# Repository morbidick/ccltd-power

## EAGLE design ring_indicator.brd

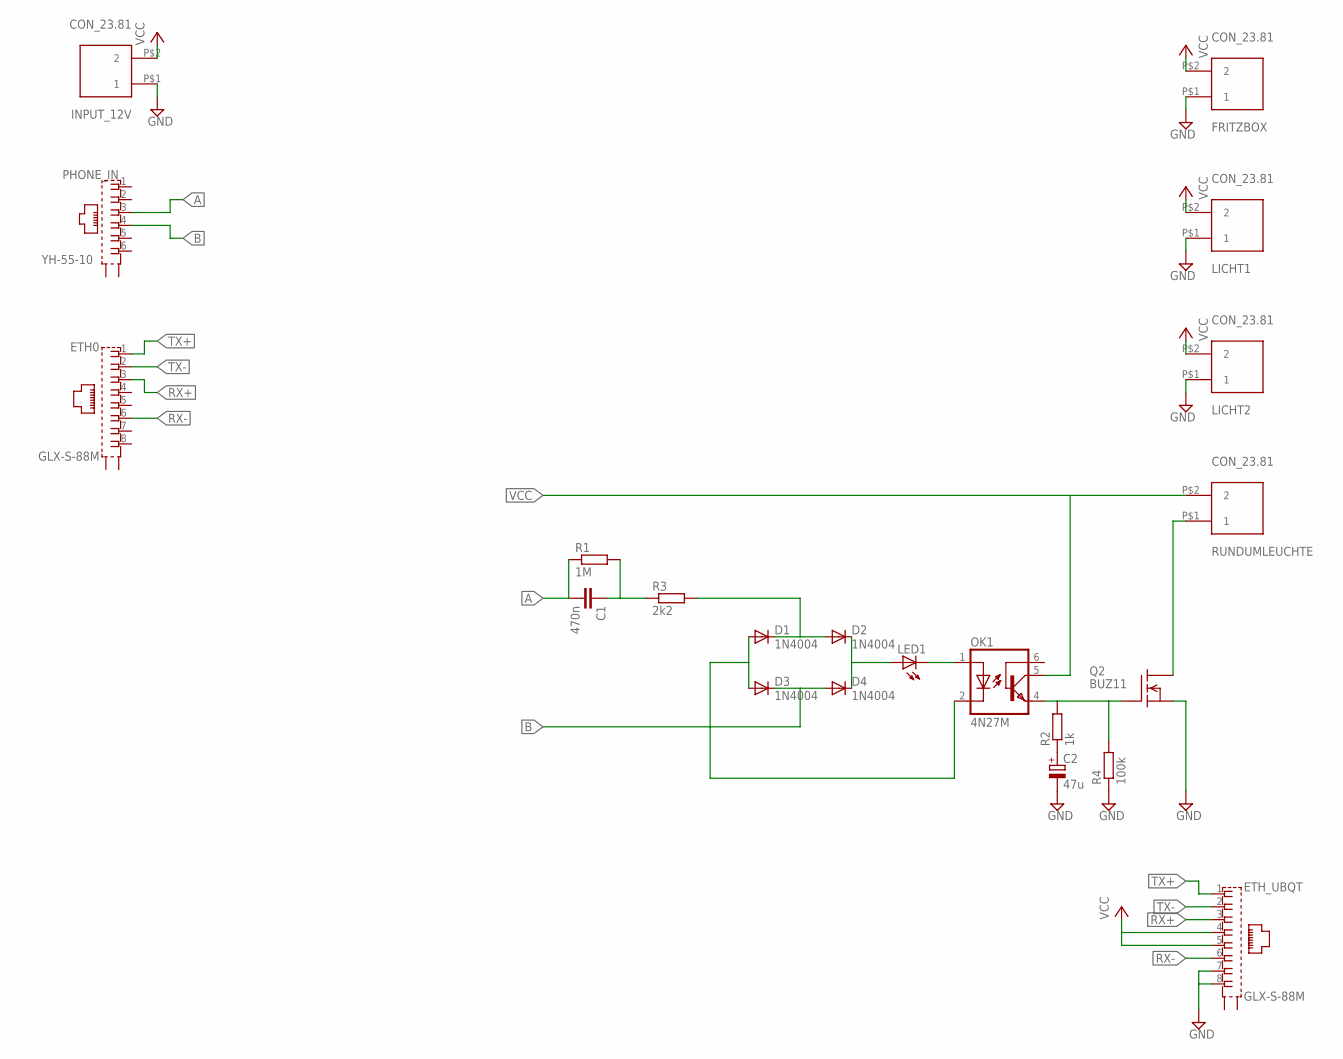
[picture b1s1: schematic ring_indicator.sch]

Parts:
C1: 470n; C102-064X133
C2: 47u; E3,5-8
D1, D2, D3, D4: 1N4004; DO41-10
ETH0: GLX-S-88M
ETH_UBQT: GLX-S-88M
FRITZBOX: CON_23.81; CON_2_3.81
INPUT_12V: CON_23.81; CON_2_3.81
LED1: LED5MM
LICHT1, LICHT2: CON_23.81; CON_2_3.81
OK1: 4N27M; DIL06
PHONE_IN: YH-55-10
Q2: BUZ11; TO220
R1: 1M; 0207/10
R2: 1k; 0207/10
R3: 2k2; 0207/10
R4: 100k; 0207/10
RUNDUMLEUCHTE: CON_23.81; CON_2_3.81

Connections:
A: C1.2, PHONE_IN.3, R1.1
B: D3.C, D4.A, PHONE_IN.4
GND: C2.-, ETH_UBQT.7, ETH_UBQT.8, FRITZBOX.P$1 (1), INPUT_12V.P$1 (1), LICHT1.P$1 (1), LICHT2.P$1 (1), Q2.3 (S), R4.1
unnamed: C1.1, R1.2, R3.1
unnamed: LED1.K (C), OK1.1 (A)
unnamed: D1.C, D2.A, R3.2
unnamed: D2.C, D4.C, LED1.A
unnamed: D1.A, D3.A, OK1.2 (C)
unnamed: Q2.2 (D), RUNDUMLEUCHTE.P$1 (1)
unnamed: OK1.4 (EMI), Q2.1 (G), R2.2, R4.2
unnamed: C2.+, R2.1
RX+: ETH0.3, ETH_UBQT.3
RX-: ETH0.6, ETH_UBQT.6
TX+: ETH0.1, ETH_UBQT.1
TX-: ETH0.2, ETH_UBQT.2
VCC: ETH_UBQT.4, ETH_UBQT.5, FRITZBOX.P$2 (2), INPUT_12V.P$2 (2), LICHT1.P$2 (2), LICHT2.P$2 (2), OK1.5 (COL), RUNDUMLEUCHTE.P$2 (2)

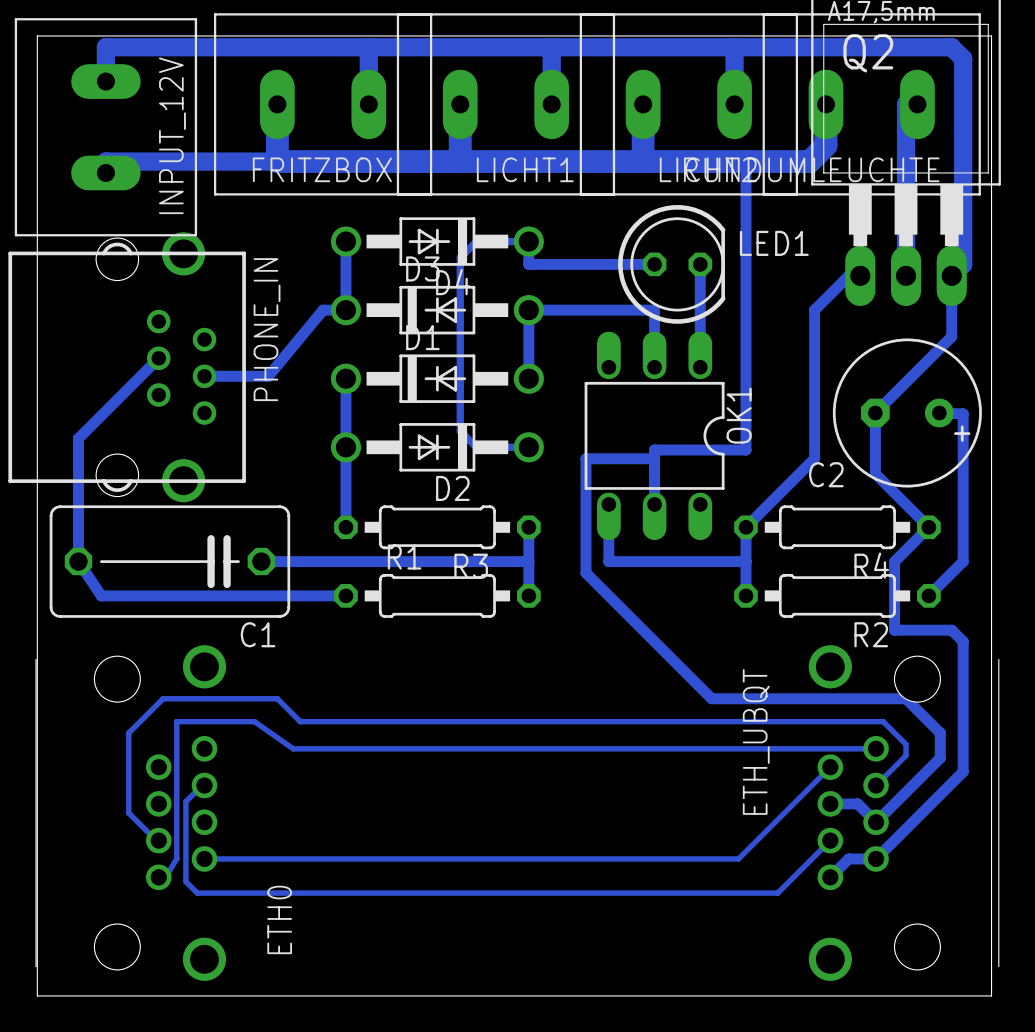
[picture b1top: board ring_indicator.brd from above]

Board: 2 copper layers, 53.5 x 53.3 mm, 21 parts (0 on the bottom side), 16 nets.

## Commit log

2016-06-23 v0.1-working
2016-06-23 v0.2-produced
2016-06-23 v0.2.1-cleanup
2016-06-23 v0.2.2-layout simplified
2016-06-24 light timing changed
2016-06-28 basic poe injector added
